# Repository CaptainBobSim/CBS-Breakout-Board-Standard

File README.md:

# CBS-Breakout-Board-Standard
The "Bob BOB" is a 2.54mm IDC Standard which allows for Arduino Based (or otherwise) modules to be easily interchanged.

See the Spreadsheet with the script here!
https://docs.google.com/spreadsheets/d/1daYPITzaq-ZQmNr3kpSN68ah_SiI3CtJoAC780Bo8d4/edit?usp=sharing

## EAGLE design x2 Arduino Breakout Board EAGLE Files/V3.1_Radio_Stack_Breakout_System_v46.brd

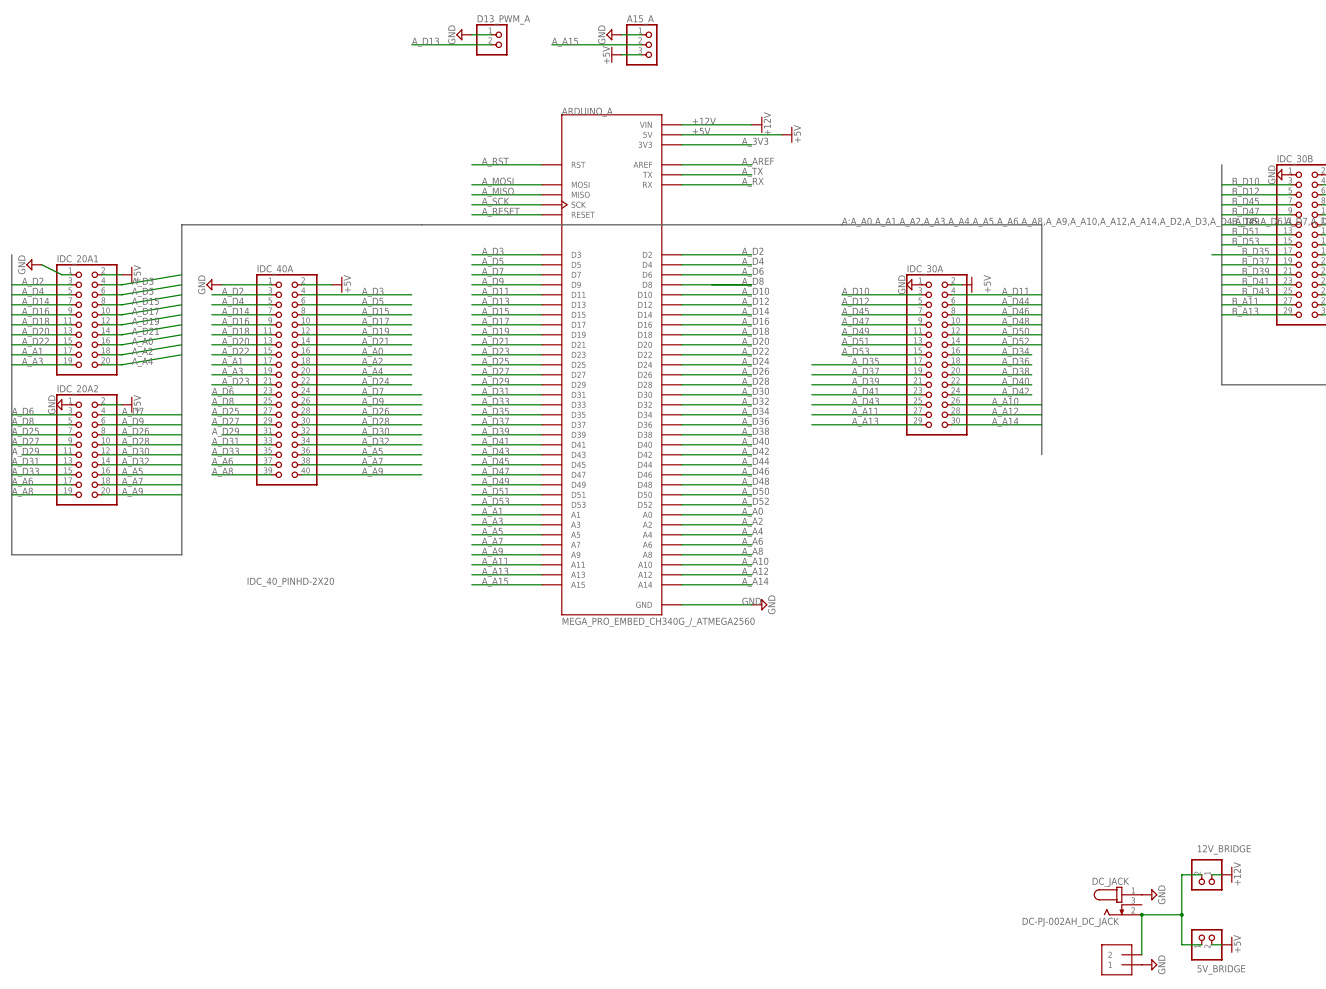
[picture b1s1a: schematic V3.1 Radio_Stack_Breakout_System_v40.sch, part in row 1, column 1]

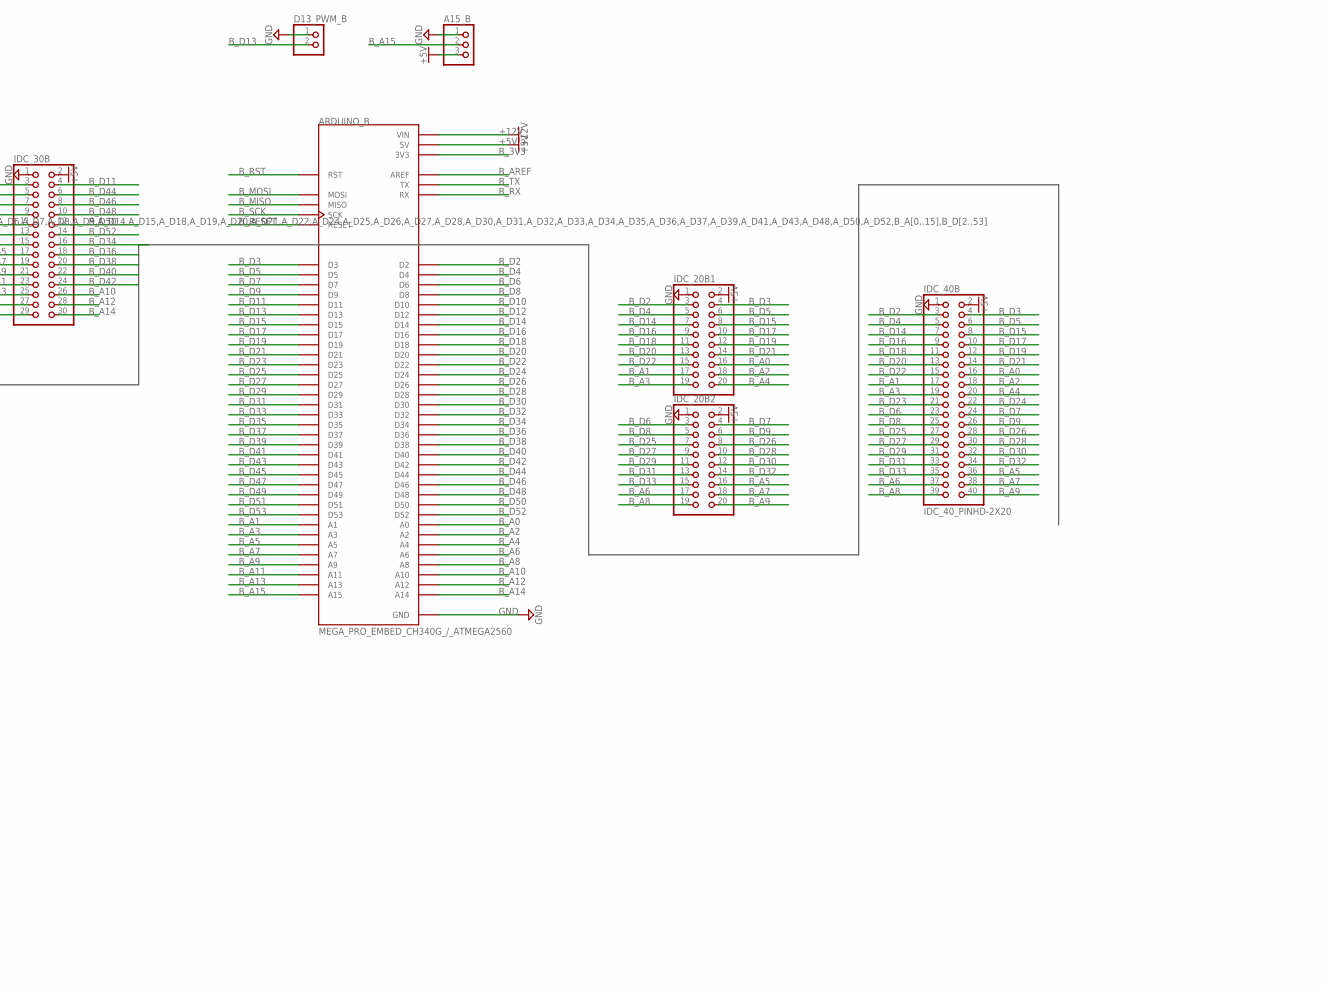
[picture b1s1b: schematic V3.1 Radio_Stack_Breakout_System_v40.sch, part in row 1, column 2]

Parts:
5V_BRIDGE, 12V_BRIDGE: PINHD-1X2; 1X02
A15_A, A15_B: PINHD-1X3; 1X03
ARDUINO_A: MEGA_PRO_EMBED_CH340G_/_ATMEGA2560; MODULE_MEGA_PRO_EMBED_CH340G_/_ATMEGA2560
ARDUINO_B: MEGA_PRO_EMBED_CH340G_/_ATMEGA2560; MODULE_MEGA_PRO_EMBED_CH340G_/_ATMEGA2560
D13_PWM_A, D13_PWM_B: PINHD-1X2; 1X02
DC_JACK: DC-PJ-002AH_DC_JACK; CUI_PJ-002AH
IDC_20A1, IDC_20A2, IDC_20B1, IDC_20B2: IDC_20_PINHD-2X10; 2X10
IDC_30A, IDC_30B: IDC_30_PINHD-2X15; 2X15_IDC_30
IDC_40A, IDC_40B: IDC_40_PINHD-2X20; IDC_40_2X20
POWER: 2.54MMAND5.08MM_SCREW_TERMINAL2.54&5.08; 1X2_2.54&5.08MM

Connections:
+5V: 5V_BRIDGE.2, A15_A.3, A15_B.3, ARDUINO_A.5V_1 (5V), ARDUINO_A.5V_2 (5V), ARDUINO_A.5V_3 (5V), ARDUINO_B.5V_1 (5V), ARDUINO_B.5V_2 (5V), ARDUINO_B.5V_3 (5V), IDC_20A1.2, IDC_20A2.2, IDC_20B1.2, IDC_20B2.2, IDC_30A.2, IDC_30B.2, IDC_40A.2, IDC_40B.2
+12V: 12V_BRIDGE.1, ARDUINO_A.VIN_1 (VIN), ARDUINO_A.VIN_2 (VIN), ARDUINO_B.VIN_1 (VIN), ARDUINO_B.VIN_2 (VIN)
A_3V3: ARDUINO_A.3V3_1 (3V3), ARDUINO_A.3V3_2 (3V3)
A_A0: ARDUINO_A.A0, IDC_20A1.16, IDC_40A.16
A_A1: ARDUINO_A.A1, IDC_20A1.17, IDC_40A.17
A_A2: ARDUINO_A.A2, IDC_20A1.18, IDC_40A.18
A_A3: ARDUINO_A.A3, IDC_20A1.19, IDC_40A.19
A_A4: ARDUINO_A.A4, IDC_20A1.20, IDC_40A.20
A_A5: ARDUINO_A.A5, IDC_20A2.16, IDC_40A.36
A_A6: ARDUINO_A.A6, IDC_20A2.17, IDC_40A.37
A_A7: ARDUINO_A.A7, IDC_20A2.18, IDC_40A.38
A_A8: ARDUINO_A.A8, IDC_20A2.19, IDC_40A.39
A_A9: ARDUINO_A.A9, IDC_20A2.20, IDC_40A.40
A_A10: ARDUINO_A.A10, IDC_30A.26
A_A11: ARDUINO_A.A11, IDC_30A.27
A_A12: ARDUINO_A.A12, IDC_30A.28
A_A13: ARDUINO_A.A13, IDC_30A.29
A_A14: ARDUINO_A.A14, IDC_30A.30
A_A15: A15_A.2, ARDUINO_A.A15
A_AREF: ARDUINO_A.AREF
A_D2: ARDUINO_A.D2, IDC_20A1.3, IDC_40A.3
A_D3: ARDUINO_A.D3, IDC_20A1.4, IDC_40A.4
A_D4: ARDUINO_A.D4, IDC_20A1.5, IDC_40A.5
A_D5: ARDUINO_A.D5, IDC_20A1.6, IDC_40A.6
A_D6: ARDUINO_A.D6, IDC_20A2.3, IDC_40A.23
A_D7: ARDUINO_A.D7, IDC_20A2.4, IDC_40A.24
A_D8: ARDUINO_A.D8, IDC_20A2.5, IDC_40A.25
A_D9: ARDUINO_A.D9, IDC_20A2.6, IDC_40A.26
A_D10: ARDUINO_A.D10, IDC_30A.3
A_D11: ARDUINO_A.D11, IDC_30A.4
A_D12: ARDUINO_A.D12, IDC_30A.5
A_D13: ARDUINO_A.D13, D13_PWM_A.2
A_D14: ARDUINO_A.D14, IDC_20A1.7, IDC_40A.7
A_D15: ARDUINO_A.D15, IDC_20A1.8, IDC_40A.8
A_D16: ARDUINO_A.D16, IDC_20A1.9, IDC_40A.9
A_D17: ARDUINO_A.D17, IDC_20A1.10, IDC_40A.10
A_D18: ARDUINO_A.D18, IDC_20A1.11, IDC_40A.11
A_D19: ARDUINO_A.D19, IDC_20A1.12, IDC_40A.12
A_D20: ARDUINO_A.D20, IDC_20A1.13, IDC_40A.13
A_D21: ARDUINO_A.D21, IDC_20A1.14, IDC_40A.14
A_D22: ARDUINO_A.D22, IDC_20A1.15, IDC_40A.15
A_D23: ARDUINO_A.D23, IDC_40A.21
A_D24: ARDUINO_A.D24, IDC_40A.22
A_D25: ARDUINO_A.D25, IDC_20A2.7, IDC_40A.27
A_D26: ARDUINO_A.D26, IDC_20A2.8, IDC_40A.28
A_D27: ARDUINO_A.D27, IDC_20A2.9, IDC_40A.29
A_D28: ARDUINO_A.D28, IDC_20A2.10, IDC_40A.30
A_D29: ARDUINO_A.D29, IDC_20A2.11, IDC_40A.31
A_D30: ARDUINO_A.D30, IDC_20A2.12, IDC_40A.32
A_D31: ARDUINO_A.D31, IDC_20A2.13, IDC_40A.33
A_D32: ARDUINO_A.D32, IDC_20A2.14, IDC_40A.34
A_D33: ARDUINO_A.D33, IDC_20A2.15, IDC_40A.35
A_D34: ARDUINO_A.D34, IDC_30A.16
A_D35: ARDUINO_A.D35, IDC_30A.17
A_D36: ARDUINO_A.D36, IDC_30A.18
A_D37: ARDUINO_A.D37, IDC_30A.19
A_D38: ARDUINO_A.D38, IDC_30A.20
A_D39: ARDUINO_A.D39, IDC_30A.21
A_D40: ARDUINO_A.D40, IDC_30A.22
A_D41: ARDUINO_A.D41, IDC_30A.23
A_D42: ARDUINO_A.D42, IDC_30A.24
A_D43: ARDUINO_A.D43, IDC_30A.25
A_D44: ARDUINO_A.D44, IDC_30A.6
A_D45: ARDUINO_A.D45, IDC_30A.7
A_D46: ARDUINO_A.D46, IDC_30A.8
A_D47: ARDUINO_A.D47, IDC_30A.9
A_D48: ARDUINO_A.D48, IDC_30A.10
A_D49: ARDUINO_A.D49, IDC_30A.11
A_D50: ARDUINO_A.D50, IDC_30A.12
A_D51: ARDUINO_A.D51, IDC_30A.13
A_D52: ARDUINO_A.D52, IDC_30A.14
A_D53: ARDUINO_A.D53, IDC_30A.15
A_MISO: ARDUINO_A.MISO
A_MOSI: ARDUINO_A.MOSI
A_RESET: ARDUINO_A.RESET
A_RST: ARDUINO_A.RST
A_RX: ARDUINO_A.RX
A_SCK: ARDUINO_A.SCK
A_TX: ARDUINO_A.TX
B_3V3: ARDUINO_B.3V3_1 (3V3), ARDUINO_B.3V3_2 (3V3)
B_A0: ARDUINO_B.A0, IDC_20B1.16, IDC_40B.16
B_A1: ARDUINO_B.A1, IDC_20B1.17, IDC_40B.17
B_A2: ARDUINO_B.A2, IDC_20B1.18, IDC_40B.18
B_A3: ARDUINO_B.A3, IDC_20B1.19, IDC_40B.19
B_A4: ARDUINO_B.A4, IDC_20B1.20, IDC_40B.20
B_A5: ARDUINO_B.A5, IDC_20B2.16, IDC_40B.36
B_A6: ARDUINO_B.A6, IDC_20B2.17, IDC_40B.37
B_A7: ARDUINO_B.A7, IDC_20B2.18, IDC_40B.38
B_A8: ARDUINO_B.A8, IDC_20B2.19, IDC_40B.39
B_A9: ARDUINO_B.A9, IDC_20B2.20, IDC_40B.40
B_A10: ARDUINO_B.A10, IDC_30B.26
B_A11: ARDUINO_B.A11, IDC_30B.27
B_A12: ARDUINO_B.A12, IDC_30B.28
B_A13: ARDUINO_B.A13, IDC_30B.29
B_A14: ARDUINO_B.A14, IDC_30B.30
B_A15: A15_B.2, ARDUINO_B.A15
B_AREF: ARDUINO_B.AREF
B_D2: ARDUINO_B.D2, IDC_20B1.3, IDC_40B.3
B_D3: ARDUINO_B.D3, IDC_20B1.4, IDC_40B.4
B_D4: ARDUINO_B.D4, IDC_20B1.5, IDC_40B.5
B_D5: ARDUINO_B.D5, IDC_20B1.6, IDC_40B.6
B_D6: ARDUINO_B.D6, IDC_20B2.3, IDC_40B.23
B_D7: ARDUINO_B.D7, IDC_20B2.4, IDC_40B.24
B_D8: ARDUINO_B.D8, IDC_20B2.5, IDC_40B.25
B_D9: ARDUINO_B.D9, IDC_20B2.6, IDC_40B.26
B_D10: ARDUINO_B.D10, IDC_30B.3
B_D11: ARDUINO_B.D11, IDC_30B.4
B_D12: ARDUINO_B.D12, IDC_30B.5
B_D13: ARDUINO_B.D13, D13_PWM_B.2
B_D14: ARDUINO_B.D14, IDC_20B1.7, IDC_40B.7
B_D15: ARDUINO_B.D15, IDC_20B1.8, IDC_40B.8
B_D16: ARDUINO_B.D16, IDC_20B1.9, IDC_40B.9
B_D17: ARDUINO_B.D17, IDC_20B1.10, IDC_40B.10
B_D18: ARDUINO_B.D18, IDC_20B1.11, IDC_40B.11
B_D19: ARDUINO_B.D19, IDC_20B1.12, IDC_40B.12
B_D20: ARDUINO_B.D20, IDC_20B1.13, IDC_40B.13
B_D21: ARDUINO_B.D21, IDC_20B1.14, IDC_40B.14
B_D22: ARDUINO_B.D22, IDC_20B1.15, IDC_40B.15
B_D23: ARDUINO_B.D23, IDC_40B.21
B_D24: ARDUINO_B.D24, IDC_40B.22
B_D25: ARDUINO_B.D25, IDC_20B2.7, IDC_40B.27
B_D26: ARDUINO_B.D26, IDC_20B2.8, IDC_40B.28
B_D27: ARDUINO_B.D27, IDC_20B2.9, IDC_40B.29
B_D28: ARDUINO_B.D28, IDC_20B2.10, IDC_40B.30
B_D29: ARDUINO_B.D29, IDC_20B2.11, IDC_40B.31
B_D30: ARDUINO_B.D30, IDC_20B2.12, IDC_40B.32
B_D31: ARDUINO_B.D31, IDC_20B2.13, IDC_40B.33
B_D32: ARDUINO_B.D32, IDC_20B2.14, IDC_40B.34
B_D33: ARDUINO_B.D33, IDC_20B2.15, IDC_40B.35
B_D34: ARDUINO_B.D34, IDC_30B.16
B_D35: ARDUINO_B.D35, IDC_30B.17
B_D36: ARDUINO_B.D36, IDC_30B.18
B_D37: ARDUINO_B.D37, IDC_30B.19
B_D38: ARDUINO_B.D38, IDC_30B.20
B_D39: ARDUINO_B.D39, IDC_30B.21
B_D40: ARDUINO_B.D40, IDC_30B.22
B_D41: ARDUINO_B.D41, IDC_30B.23
B_D42: ARDUINO_B.D42, IDC_30B.24
B_D43: ARDUINO_B.D43, IDC_30B.25
B_D44: ARDUINO_B.D44, IDC_30B.6
B_D45: ARDUINO_B.D45, IDC_30B.7
B_D46: ARDUINO_B.D46, IDC_30B.8
B_D47: ARDUINO_B.D47, IDC_30B.9
B_D48: ARDUINO_B.D48, IDC_30B.10
B_D49: ARDUINO_B.D49, IDC_30B.11
B_D50: ARDUINO_B.D50, IDC_30B.12
B_D51: ARDUINO_B.D51, IDC_30B.13
B_D52: ARDUINO_B.D52, IDC_30B.14
B_D53: ARDUINO_B.D53, IDC_30B.15
B_MISO: ARDUINO_B.MISO
B_MOSI: ARDUINO_B.MOSI
B_RESET: ARDUINO_B.RESET
B_RST: ARDUINO_B.RST
B_RX: ARDUINO_B.RX
B_SCK: ARDUINO_B.SCK
B_TX: ARDUINO_B.TX
GND: A15_A.1, A15_B.1, ARDUINO_A.GND_1 (GND), ARDUINO_A.GND_2 (GND), ARDUINO_A.GND_3 (GND), ARDUINO_B.GND_1 (GND), ARDUINO_B.GND_2 (GND), ARDUINO_B.GND_3 (GND), D13_PWM_A.1, D13_PWM_B.1, DC_JACK.1, IDC_20A1.1, IDC_20A2.1, IDC_20B1.1, IDC_20B2.1, IDC_30A.1, IDC_30B.1, IDC_40A.1, IDC_40B.1, POWER.1, POWER.P$1 (1)
unnamed: 5V_BRIDGE.1, 12V_BRIDGE.2, DC_JACK.2, POWER.2, POWER.P$2 (2)

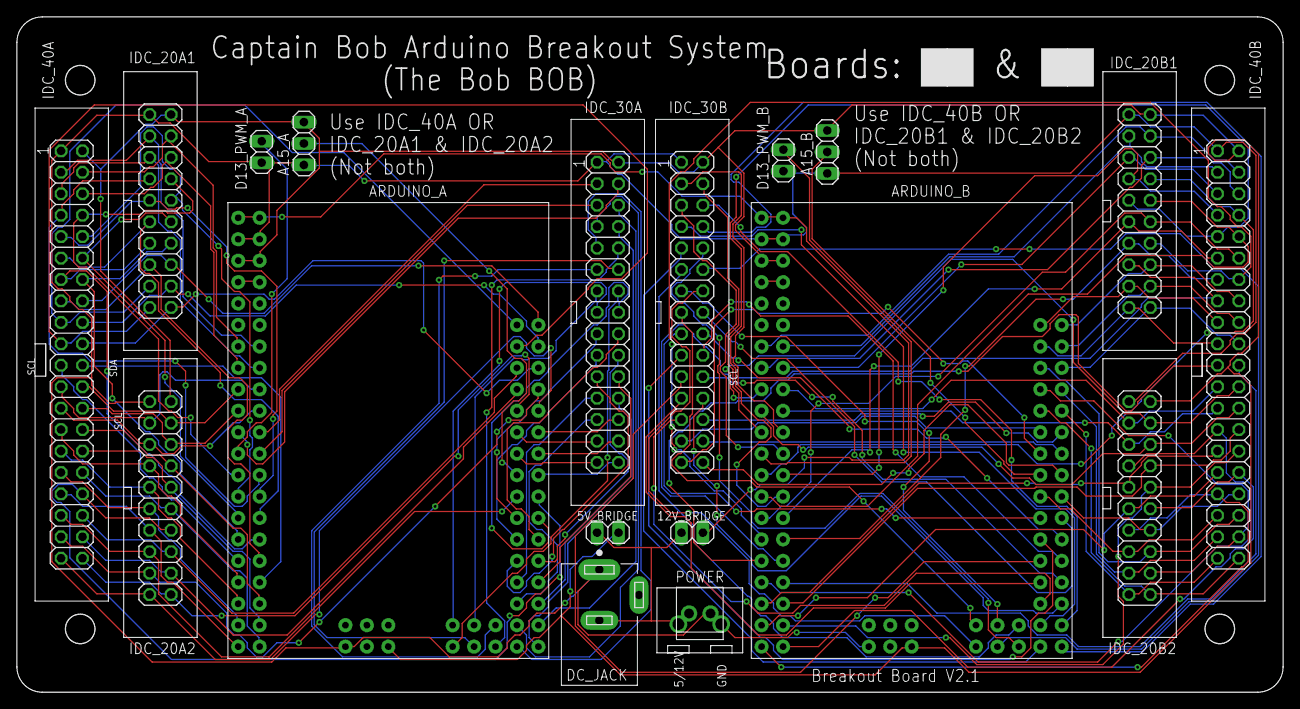
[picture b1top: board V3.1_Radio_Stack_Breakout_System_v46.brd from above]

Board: 2 copper layers, 150.0 x 80.0 mm, 18 parts (0 on the bottom side), 142 nets.

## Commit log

2025-02-24 Initial Publishing
2025-02-24 Organize Files for Usability and Add Gerber files
